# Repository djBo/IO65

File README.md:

# IO/65

IO/65, a modular hardware platform for the 6502 processor.

This project is very much inspired by [RC2014](https://rc2014.co.uk/) and Ben Eater's 6502 YouTube series.

### Table of Contents

   1. [History](#history)
   2. [Design](#design)
      * [Dimensions](#dimensions)
      * [Pinout](#pinout)
      * [Memory Map](#memory-map)
   3. [Boards](#boards)
      * [Backplane](#backplane)
      * [CPU](#cpu)
      * [Decoder](#address-decoder)
      * [Memory](#memory-module)
      * [VIA](#via)
      * [RIOT](#riot)
      * [Work in progress](#work-in-progress)
         - [ACIA](#acia)
         - [Audio](#audio)
         - [Banked Memory #1](#banked-memory-1)
         - [Banked Memory #2](#banked-memory-2)
         - [Buffered Memory](#buffered-memory)
         - [Dual-Port Memory](#dual-port-memory)
         - [Interrupt Controller](#interrupt-controller)
         - [PGA2040 Device](#pga2040-device)
         - [PGA2040 Emulator](#pga2040-emulator)
         - [Spy](#spy)
         - [Tape Interface](#tape-interface)
         - [UART](#uart-from-scratch)
         - [Video](#video-board)
         - [PC/104](#pc104)
      * [SBC](#sbc)
   4. [Footnotes](#footnotes)

### History

In the middle of the 2010's, I saved an Apple II-c from a dumpster. Sadly, without power supply, monitor or even software, there was no possibility of booting it directly.  
After a few searches on the interwebz, I came accross a breadboard circuit, allowing the 6502 in free running mode. So, I carefully removed the NCR 6502 CPU from it's socket, and placed it on a breadboard. I wired everything up, using a 555 as a rudimentary clock and a bunch of led bars on the address and data bus. I was intrigued by the flashy lights.

Then I stuble accross the [6502 primer](http://wilsonminesco.com/6502primer/)...  
It's a disguised Pandora's box! Inside you'll find an endless supply of more boxes, each containing countless more. It's a rabbit hole that never ends. Each box is a tiny bit of knowledge about a given subject you need to understand. The further you go, the more you need to figure out.

And so, starting with limited supplies, I opened the first box. The rest is history.

### Design

The original proof-of-concept board was based around the same use of angled pin headers as on RC2014. However, bent pins were a constant source of problems, not to mention the lack in quantity. Dual row headers were also considered, but this came with it's own connector problem of being very hard to remove and the increased risk of more bent pins. The set dimensions of the 40-pin wide header made the boards clunky. This meant that a simply back plane would quickly fall outside the cheapest 10x10mm manufacturing pricing.

The final design is centered around two specific standards:

 - the [ISO/IEC 7810](https://en.wikipedia.org/wiki/ISO/IEC_7810) standard, specifying the size of credit cards (amongst others) at 85.6mm by 53.98mm or 3+3⁄8" by 2+1⁄8". This was mostly inspired by several 6502 badges and the idea to carry one "in your wallet".
 - the PC/XT [ISA bus](https://en.wikipedia.org/wiki/Industry_Standard_Architecture) connector (a.k.a. [J1](https://nl.mouser.com/ProductDetail/571-6-5530843-5)). This was inspired by the fact that the edge connector width fits nicely in the middle of the card. A nice coincedence, is that the connector itself is pretty much as wide as the board, making them site nice and flush.

#### Dimensions

- Board: 85.6x54 mm
- Top corner radius: 3 mm
- Bottom corner radium: 1 mm
- Edge connector width: 81 mm
- Edge connector height: 300 mil
- Edge connector chamfer: 0,5 mm
- Edge connector bevelled: yes
- Edge connector location: bottom, centered on pin 16/47
- Thumb pocket radius: 13 mm
- Thumb pocket center: 10 mm from the top, 12 mm from the edge
- Work area center: 3,5 mm above card center
- Preferred OSHW logo location: 9,5 mm from the top, 10 mm from the right edge

An optional 2 mm wide cut-out slot on pin 17/48 is taken into account in the designs of the individual boards, forcing the board in a single direction. While the current backplane connects these pins allowing the boards to be rotated, it should be noted that __all boards need to face the same direction__ for the system to operate correctly.

#### Pinout

| Pin (Front) | Function | Pin (Back) | Function |
|----|----|----|----|
| 1 | GND | 32 | A0 |
| 2 | +5V | 33 | A1 |
| 3 | Φ2 | 34 | A2 |
| 4 | R/<span style="text-decoration: overline;">W</span> | 35 | A3 |
| 5 | <span style="text-decoration: overline;">RES</span> | 36 | A4 |
| 6 | RDY | 37 | A5 |
| 7 | <span style="text-decoration: overline;">IRQ</span> | 38 | A6 |
| 8 | <span style="text-decoration: overline;">NMI</span> | 39 | A7 |
| 9 | D0 | 40 | A8 |
| 10 | D1 | 41 | A9 |
| 11 | D2 | 42 | A10 |
| 12 | D3 | 43 | A11 |
| 13 | D4 | 44 | A12 |
| 14 | D5 | 45 | A13 |
| 15 | D6 | 46 | A14 |
| 16 | D7 | 47 | A15 |
| 17 | **NC** | 48 | **NC** |
| 18 | <span style="text-decoration: overline;">OE</span> | 49 | Unused [^1] |
| 19 | <span style="text-decoration: overline;">WE</span> | 50 | Unused |
| 20 | <span style="text-decoration: overline;">CS0</span> | 51 | VIA CB1 |
| 21 | <span style="text-decoration: overline;">CS1</span> | 52 | VIA CB2 |
| 22 | <span style="text-decoration: overline;">CS2</span> | 53 | VIA PB0 / RIOT PA0 |
| 23 | <span style="text-decoration: overline;">CS3</span> | 54 | VIA PB1 / RIOT PA1 |
| 24 | <span style="text-decoration: overline;">CS4</span> | 55 | VIA PB2 / RIOT PA2 |
| 25 | <span style="text-decoration: overline;">CS5</span> | 56 | VIA PB3 / RIOT PA3 |
| 26 | <span style="text-decoration: overline;">CS6</span> | 57 | VIA PB4 / RIOT PA4 |
| 27 | <span style="text-decoration: overline;">CS7</span> | 58 | VIA PB5 / RIOT PA5 |
| 28 | <span style="text-decoration: overline;">CS8</span> | 59 | VIA PB6 / RIOT PA6 |
| 29 | <span style="text-decoration: overline;">CS9</span> | 50 | VIA PB7 / RIOT PA7 |
| 30 | <span style="text-decoration: overline;">CS10</span> | 61 | +5V |
| 31 | <span style="text-decoration: overline;">CS11</span> | 62 | GND |

[^1]: For the two unused pins there are two possible options: serial Rx/Tx lines connected to the USB header on the back plane, or I^2^C.

#### Memory Map

Using the 6502 primer as guidance, the following design should be easy to implement and extend:

| Range | Description |
|---|---|
| 0x000-0x7FFF | 32K RAM |
| 0x8000-0x9FFF | 8K expansion (<span style="text-decoration: overline;">CS0</span>) |
| 0xA000-0xBFFF | 8K expansion (<span style="text-decoration: overline;">CS1</span>) |
| 0xC000-0xDFFF | 8K expansion (<span style="text-decoration: overline;">CS2</span>) |
| 0xE000-0xFFFF | 8K ROM (<span style="text-decoration: overline;">CS3</span>) |

### Boards

#### Backplane

The current iteration of the backplane crudely ties all lines of 8 slots (600 mil apart) together, exposing power pins through a two-pin header and optionally a MicroUSB connector, with data lines on another two-pin header. While it can certainly be used for initial design verification, it clearly needs a few upgrades like real power delivery and status leds.

#### CPU

The CPU board contains the 6502, 1MHz crystal, and a debounced button for the reset circuit. It can be configured to be used with either older or newer CPU's, reconfiguring the pins for BE and <span style="text-decoration: overline;">VP</span>. It exposes the oscillator output, Φ0 input, and the SYNC/<span style="text-decoration: overline;">SO</span>/<span style="text-decoration: overline;">VP</span>/BE signals to a 6-pin header. They can be used to provide external clocks or single-cycle/single-instruction stepping capabilities.

Under normal use, a jumper should connect the oscillator output and Φ0 input together.

#### Address Decoder

The address decoder is responsible for providing a usuable memory map, and providing signals for <span style="text-decoration: overline;">OE</span>, <span style="text-decoration: overline;">WE</span> and <span style="text-decoration: overline;">CS0</span> to <span style="text-decoration: overline;">CS11</span>.

<span style="text-decoration: overline;">OE</span> and <span style="text-decoration: overline;">WE</span> are generated by using R/<span style="text-decoration: overline;">W</span> and Φ2. <span style="text-decoration: overline;">CS0</span> to <span style="text-decoration: overline;">CS3</span> are directly mapped to the first stage decoder, giving each section 8k (see the [memory map](#memory-map) above).

The second stage decoder breaks the 0xC000-0xDFFF range down into 8 sections of 1k. These are exposed on a separate 8-pin header.  
The third stage decoder breaks down two configurable regions into 4 sections of 256 bytes. These two ranges are tied into <span style="text-decoration: overline;">CS4</span> to <span style="text-decoration: overline;">CS11</span>:

| Region | 3 | ∆ |
|---|---|---|
| 1 | 0xC000-0xC3FF | 0xD800-0xDBFF |
| 2 | 0xD000-0xD3FF | 0xDC00-oxDFFF |

#### Memory Module

The memory module is a configurable 8k or 32k single chip (DIP28) design, allowing it to be placed in either the RAM range or any of the 8k ranges. An optional 2-pin dip-switch or header can be soldered to accommodate 32k EEPROMS with manual banking.

#### VIA

The Versatile Interface Adapter (a.k.a. 6522) provides 2 16-bit programmable timers and two 8-bit ports with two control lines each. It exposes PORTA and control lines on a 10-pin header and PORTB and control lines on the rear of the edge connector. PORTB was chosen as it is connected to the onboard shift register, allowing extended capabilities in combination with other board circuits.

#### RIOT

The RAM, IO and Timer (a.k.a. 6532) provides 128 bytes of general purpose RAM, programmable interval timer and two 8-bit IO ports. It exposes PORTB on an 8-pin header and PORTA on the rear of the edge connector. While PORTB can drive more current (and thus more suited for driving external circuitry), PORTA has an additional edge-detect capability on PA7.

#### Work in progress

The following boards are very much *in development*:

##### ACIA

The Asynchronous Communications Interface Adapter (a.k.a. 6551) provides serial communication. It is intended to be used with a Serial-to-USB device.

##### Audio

The audio board consists of two [SN76489](https://en.wikipedia.org/wiki/Texas_Instruments_SN76489)'s for stereo 3 channel PSG and 1 channel noise.

##### Banked Memory #1

This board banks 2 MB of RAM in 256 8k blocks. This is specifically meant for <span style="text-decoration: overline;">CS1</span> or <span style="text-decoration: overline;">CS2</span>.

##### Banked Memory #2

This board banks 8 MB in 256 32k blocks. This is specifically meant to occupy the RAM region.

##### Buffered Memory

This board contains 2 8k RAM chips. All control lines are attached in a cross fashion to both the edge connector and a 22-pin header for external circuitry. While one chip is connected to the edge, the other is connected to the header. Ths can be swicthed using a single 1-bit register. This is specifically meant for the <span style="text-decoration: overline;">CS2</span> region in conjuncion with the below mentioned video output card.

##### Dual-Port Memory

This board contains a single dual-port 8k SRAM ic. One side is connected to the edge connector (read/write), while the other is exposed on a 22-pin header for external circuitry. This is specifically meant for the <span style="text-decoration: overline;">CS2</span> region in conjuncion with the below mentioned video output card.

##### Interrupt Controller

This board is from Paul Fellingham's [design](http://6502.org/mini-projects/priority-interrupt-encoder/priority-interrupt-encoder.html), and provides 8 prioritized interrupt inputs on a header.  
Future designs of interrupt capable boards will introduce additional configuration options and IRQ line exposure using a single pin header (similar to how CS is done).

##### PGA2040 Device

This board contains a [PGA2040](https://shop.pimoroni.com/products/pga2040) with 10 pins connected through voltage converters to CS, R/W and data bus signals. This board is meant to be utilized as an addressable device.

##### PGA2040 Emulator

This board contains a [PGA2040](https://shop.pimoroni.com/products/pga2040) utilizing all 30 available pins to the edge connector. This board is meant as a CPU replacement, and act as a full-scale 6502 emulator.

##### Spy

The Spy board contains all the required circuitry to implement adjustable clocks, single-cycle/single-instruction stepping and a hexadecimal display of the address/data bus values using TIL311's. This board is explicitly meant to be used in conjunction with a new 65C02 CPU with the BE and <span style="text-decoration: overline;">VP</span> pins. **Do not use with NMOS 6502's!**

##### Tape Interface

This board implements a Kansas City Standard tape decoder interface. See [this project](https://www.gregorystrike.com/2023/01/07/kansas-city-standard-decoder/) and this [Hackaday topic](https://hackaday.com/2022/10/11/a-cassette-interface-for-a-6502-breadboard-computer-kansas-city-style/) for more information.

##### UART from scratch

The board is based on James Sharman's amazing youtube series [UART from scratch](https://www.youtube.com/watch?v=aE5VTp_eMN4&list=PLFhc0MFC8MiCs8W5H0qZlC6QNbpAAe_O-&pp=iAQB).

##### Video Board

This board contains a [MC6847](https://en.wikipedia.org/wiki/Motorola_6847) VDG with a MC1372 modulator, and can be used to output a video signal. It is meant to be used together with the above mentioned Buffered Memory or Dual-Port Memory boards. All designs come straight from [@pmig96](https://twitter.com/pmig96)'s series of articles on the subject:

* [MC6874 Test Circuit #1](https://pmig96.wordpress.com/2020/07/15/mc6847-test-circuit/)
* [MC6874 Test Circuit #2](https://pmig96.wordpress.com/2020/07/16/mc6847-test-circuit-part-2/)
* [MC6874 Test Circuit #3](https://pmig96.wordpress.com/2020/07/24/mc6847-test-circuit-part-3/)
* [MC6874 Test Circuit #4](https://pmig96.wordpress.com/2020/07/27/mc6847-test-circuit-part-4/)
* [MC6874 Test Circuit #5](https://pmig96.wordpress.com/2022/04/01/mc6847-test-circuit-part-5/)
* [MC6874 Test Circuit #6](https://pmig96.wordpress.com/2022/04/05/mc6847-test-circuit-part-6/)
* [MC6874 Test Circuit #7](https://pmig96.wordpress.com/2022/04/07/mc6847-test-circuit-part-7/)
* [MC6874 Test Circuit #8](https://pmig96.wordpress.com/2022/08/22/mc6847-test-circuit-part-8/)
* [MC6874 Dual-Port RAM](https://pmig96.wordpress.com/2020/08/20/a-dual-ported-ram-for-the-mc6847/)

Sadly, there is not much info out there regarding this chip. Worst of all, mine *seems* to be misbehaving, as I am not able to reproduce the nice black-and-white image from part 1 (it's all wavy side to side).

##### PC/104

This board is mostly a proof-of-concept, trying to adapt the 6502 platform to the the PC/104 form-factor. While not all signals can be re-created, most of them can be provided.

#### SBC

This board is designed to combined several cards into a single-board-computer and uses only SMD components. It's meant to be a badge, capable of running from a single 18550 battery. This is the culmination of months of designing all the other boards, and making a version that has everything already integrated. By utilizing the tiniest of chips, the board is capable of housing a fairly involved set of capabilities.

**Features:**

* QFN-44 packaged WDC 65C02 CPU
* QFN-44 packaged WDC 65C22 VIA
* 1MHz Clock
* 32Kb SRAM
* 8Kb FRAM
* configurable decoder logic
* single-cycle/single-instruction stepping
* blinkin' leds everywhere
* powered by USB or 18650 battery with seemless switching
* battery charging with USB or solar
* firmware upgrading through USB

**Design considerations:**  
Almost none of these parts can be hand-soldered, so stencils for both sides are required. Note the use of 0402 sized resistors, capacitors and leds. The board complexity also requires at least 4 layers, with real layer-to-layer via's.

For power delivery, a simple integrated ic would be nice. However, a single ic incorporating USB/Solar charging, buck-boost conversion, seemless switching and interrupt capability might prove hard to find. Any suggestions are welcome.

Firmware upgrading is an entire new can-o-worms. Some FTDI chips seem to be capable of doing the job, but custom host-based software will probably be required. It will need to connect to the BE signal (and possibly RST/RDY too) in order to take full bus-control. Another contention issue is the size and pricing of FRAM: 32K is about $ 14 each, while 8k is about half.

While the WDC 65C51N is available is a nice QFP-32 package, it suffers from the transmit data register bug and was omitted in the initial design. Also, Mouser only has the DIP & PLCC versions.

LED control could possibly be accomplished with the VIA PORTB's shift-register feature. This would mean swapping the ports around from the original board and needs some serious reconsideration before going down that route.  
The core mechanic is to provide generic control using PORTA, optionally extending it to hardware based RGB control.

Memory could possibly be increased by adding one or two cheap 8k SRAM ic's. 

**BoM**:

| Nr | Description | Part Nr. | Power | Price |
|---|---|---|---|---|
| 1 | WDC 65C02 | [W65C02S6TQG-14](https://nl.mouser.com/ProductDetail/955-W65C02S6TQG-14) | 150uA@1MHz | € 9,88 |
| 1 | WDC 65C02 | [W65C22S6TQG-14](https://nl.mouser.com/ProductDetail/955-W65C22S6TQG-14) || € 10,21 |
| 1 | FRAM 8Kb | [FM16W08-SG](https://nl.mouser.com/ProductDetail/877-FM16W08-SG) || € 6,50 |
| 1 | SRAM 32Kb | [AS7C256A-10TCN](https://nl.mouser.com/ProductDetail/913-AS7C256A-10TCN) || € 2,30 |
| 1 | 1MHz Oscillator | [LFSPXO058610Reel](https://nl.mouser.com/ProductDetail/449-LFSPXO058610REEL) or [CB3-3C-1M000000](https://nl.mouser.com/ProductDetail/774-CB3-3C-1M000000) || € 1,36 / 1,59 |
| 1 | Battery Management IC | [MAX8903](https://nl.mouser.com/ProductDetail/700-MAX8903DETI+) || € 7,06 |
| 8 | Green LED 0402 | Data Bus || ... |
| 16 | Red LED 0402 | Address Bus || ... |
| 8 | White, Blue or RGB LED 0402 | VIA PORT A || ... |
| 2 | Inverter | [SN74AHCT1G04DBVR](595-SN74AHCT1G04DBVR) SOT-23-5 || € 0,348 |
| 2 | Dual 2-to-4 line decoder | [SN74HCT139DE4](https://nl.mouser.com/ProductDetail/595-SN74HCT139DE4) || € 1,21 |
| 1 | 3-to-8 line decoder | [MC74HCT138ADG](https://nl.mouser.com/ProductDetail/863-MC74HCT138ADG) || €  |
| 1 | USB-to-Parallel | [FT245RL](https://nl.mouser.com/ProductDetail/895-FT245RL) (SSOP-28) or [FT245RQ](https://nl.mouser.com/ProductDetail/895-FT245RQ-TRAY) (QFN-32) || € 4,51 |
| 1 | SRAM 2Mb | [CY62167GN-45ZXI](https://nl.mouser.com/ProductDetail/727-CY62167GN-45ZXI) || € 13,24 |

To be considered:
| Nr | Description | Part Nr. | Price |
|---|---|---|---|
| 1 | 18650 Battery Clip | [12BHC186P1-GR](https://nl.mouser.com/ProductDetail/12BHC186P1-GR) | € 3,30 |
| 1 | Solar Battery Charger IC | [SPV1040T](https://nl.mouser.com/ProductDetail/511-SPV1040T) | € 4,19 |
| 1 | 3.3V Voltage Reference | [MCP1501T-33E/CHY](https://nl.mouser.com/ProductDetail/579-MCP1501T-33E/CHY) | € 0.94 |
| 1 | 3.3V Voltage Reference | [MAX6070BAUT33+T](https://nl.mouser.com/ProductDetail/700-MAX6070BAUT33T) | € 2.61 |
| 1 | 3.3V Voltage Reference | [ADR3533WARMZ-R7](https://nl.mouser.com/ProductDetail/584-ADR3533WARMZ-R7) | € 3.72 |
| 1 | 3.3V Voltage Reference | [ADR4533ARZ](https://nl.mouser.com/ProductDetail/584-ADR4533ARZ) | € 7.36 |
| 8 | Tri-Color LED | [APGF1012GBRC-07](https://nl.mouser.com/ProductDetail/604-APGF1012GBRC-07) | € 0,987 |
| 8 | RGB LED | [LRTBR48G-P9Q7-1+R7S5-26+NP-68](https://nl.mouser.com/ProductDetail/720-LRTBR48GP9A3521) | € 0,385 |
| 1 | USB Type-C Connector | | € 0,63 + |
| 1 | Parallel I^2^C Controller | [PCF8584T/2,512](https://nl.mouser.com/ProductDetail/771-PCF8584T2512) | € 6,58 |

### Footnotes

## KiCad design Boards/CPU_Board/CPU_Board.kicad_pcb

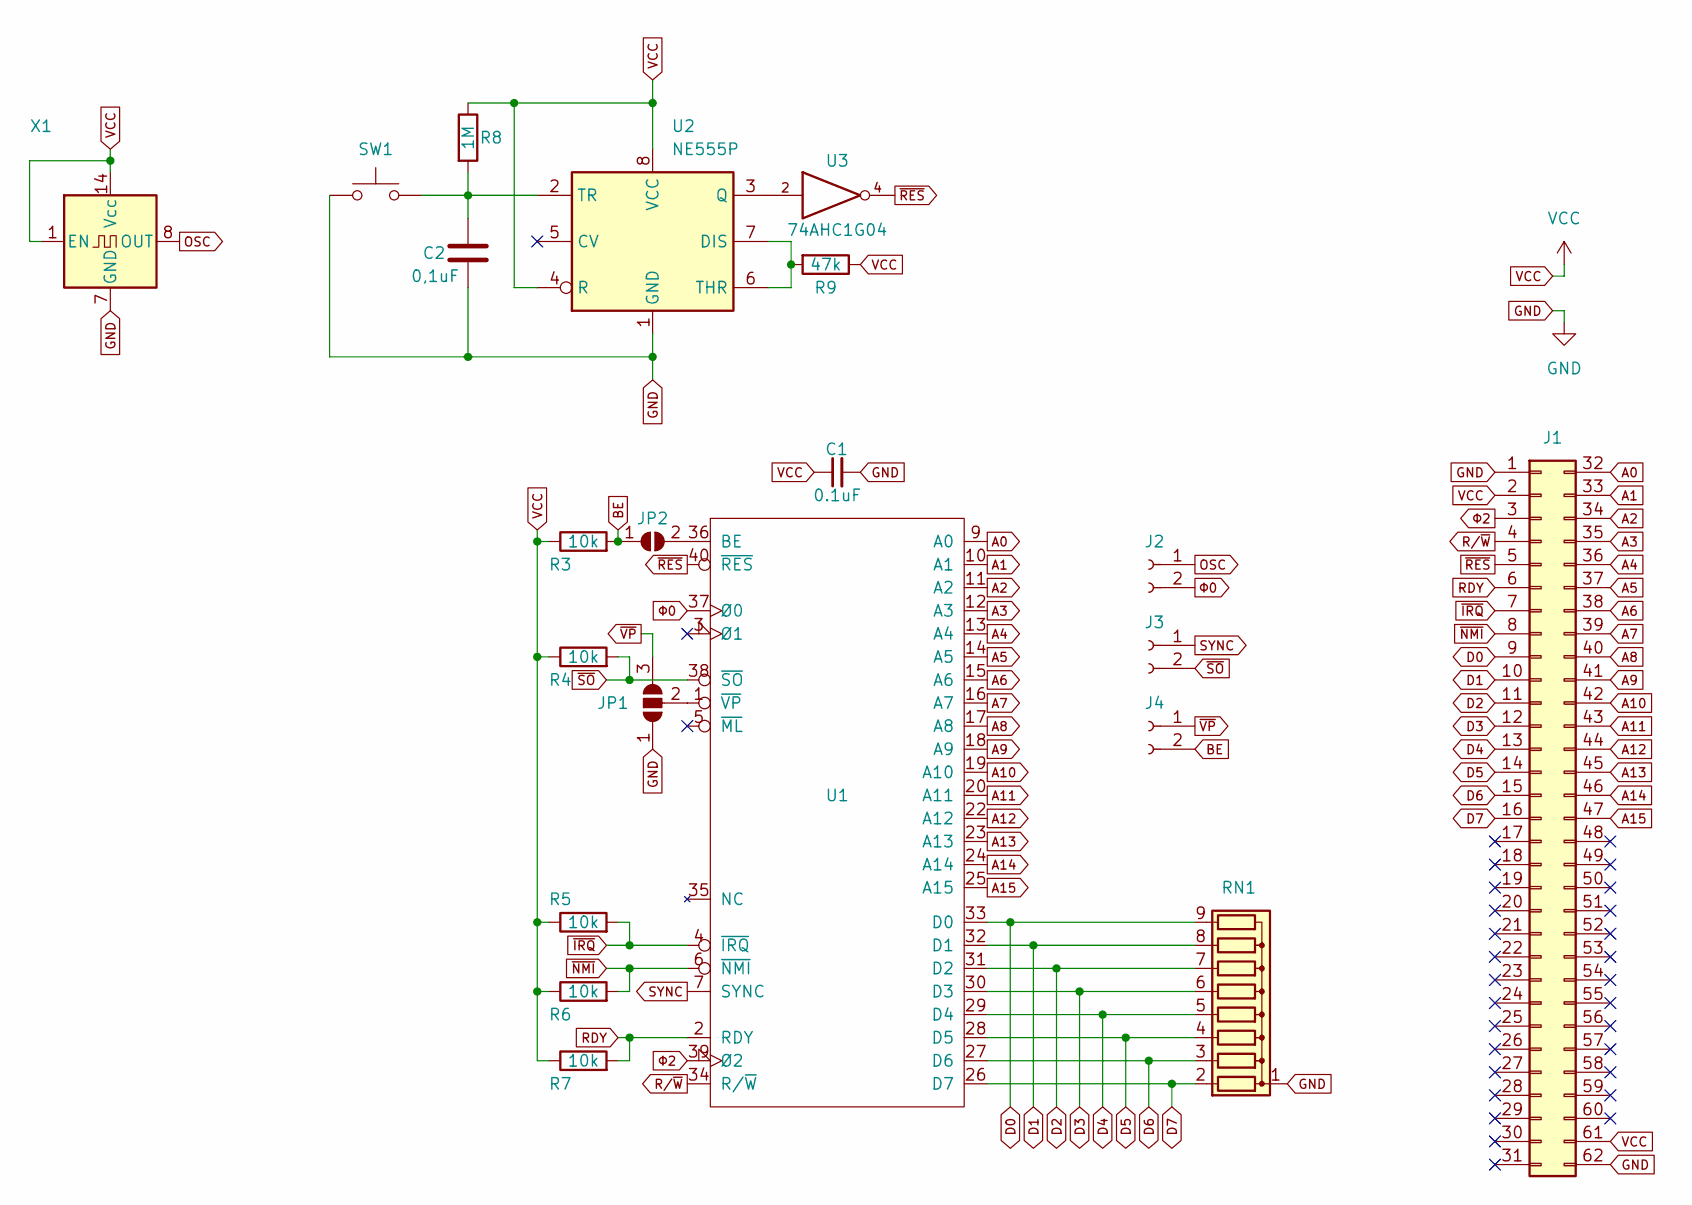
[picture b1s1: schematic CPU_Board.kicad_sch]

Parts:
C1: 0.1uF; C_Disc_D4.7mm_W2.5mm_P5.00mm
C2: 0,1uF; C_Disc_D4.7mm_W2.5mm_P5.00mm
J1: Edge Connector; BUS_PC_M
J2, J3, J4: Conn_01x02_Female; PinSocket_1x02_P2.54mm_Horizontal
JP1: SolderJumper_3_Open; SolderJumper-3_P1.3mm_Open_Pad1.0x1.5mm
JP2: SolderJumper_2_Open; SolderJumper-2_P1.3mm_Open_Pad1.0x1.5mm
R3, R4, R5, R6, R7: 10k; R_Axial_DIN0207_L6.3mm_D2.5mm_P7.62mm_Horizontal
R8: 1M; R_Axial_DIN0207_L6.3mm_D2.5mm_P7.62mm_Horizontal
R9: 47k; R_Axial_DIN0207_L6.3mm_D2.5mm_P7.62mm_Horizontal
RN1: 10k; R_Array_SIP9
SW1: SW_Push; SW_Tactile_SPST_Angled_PTS645Vx39-2LFS
U1: WDC65C02_DIP; DIP-40_W15.24mm_Socket
U2: NE555P; DIP-8_W7.62mm_Socket
U3: 74AHC1G04; SOT-23-5
X1: CXO_DIP14; Oscillator_DIP-14

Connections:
A0: J1.32, U1.9 (A0)
A1: J1.33, U1.10 (A1)
A2: J1.34, U1.11 (A2)
A3: J1.35, U1.12 (A3)
A4: J1.36, U1.13 (A4)
A5: J1.37, U1.14 (A5)
A6: J1.38, U1.15 (A6)
A7: J1.39, U1.16 (A7)
A8: J1.40, U1.17 (A8)
A9: J1.41, U1.18 (A9)
A10: J1.42, U1.19 (A10)
A11: J1.43, U1.20 (A11)
A12: J1.44, U1.22 (A12)
A13: J1.45, U1.23 (A13)
A14: J1.46, U1.24 (A14)
A15: J1.47, U1.25 (A15)
BE: J4.2, JP2.1 (A), R3.2
D0: J1.9, RN1.9 (R8), U1.33 (D0)
D1: J1.10, RN1.8 (R7), U1.32 (D1)
D2: J1.11, RN1.7 (R6), U1.31 (D2)
D3: J1.12, RN1.6 (R5), U1.30 (D3)
D4: J1.13, RN1.5 (R4), U1.29 (D4)
D5: J1.14, RN1.4 (R3), U1.28 (D5)
D6: J1.15, RN1.3 (R2), U1.27 (D6)
D7: J1.16, RN1.2 (R1), U1.26 (D7)
GND: C1.2, C2.2, J1.1, J1.62, JP1.1 (A), RN1.1 (common), SW1.1, U1.21 (GND), U2.1 (GND), U3.3 (GND), X1.7 (GND)
unnamed: C2.1, R8.2, SW1.2, U2.2 (TR)
unnamed: JP1.2 (C), U1.1 (~VP)
unnamed: JP2.2 (B), U1.36 (BE)
unnamed: R9.2, U2.6 (THR), U2.7 (DIS)
unnamed: U2.3 (Q), U3.2
OSC: J2.1, X1.8 (OUT)
RDY: J1.6, R7.2, U1.2 (RDY)
SYNC: J3.1, U1.7 (SYNC)
VCC: C1.1, J1.2, J1.61, R3.1, R4.1, R5.1, R6.1, R7.1, R8.1, R9.1, U1.8 (VCC), U2.4 (R), U2.8 (VCC), U3.5 (VCC), X1.1 (EN), X1.14 (Vcc)
~IRQ: J1.7, R5.2, U1.4 (~IRQ)
~NMI: J1.8, R6.2, U1.6 (~NMI)
~RES: J1.5, U1.40 (~RES), U3.4
~SO: J3.2, R4.2, U1.38 (~SO)
~VP: J4.1, JP1.3 (B)
Φ0: J2.2, U1.37 (Ø0)
Φ2: J1.3, U1.39 (Ø2)

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
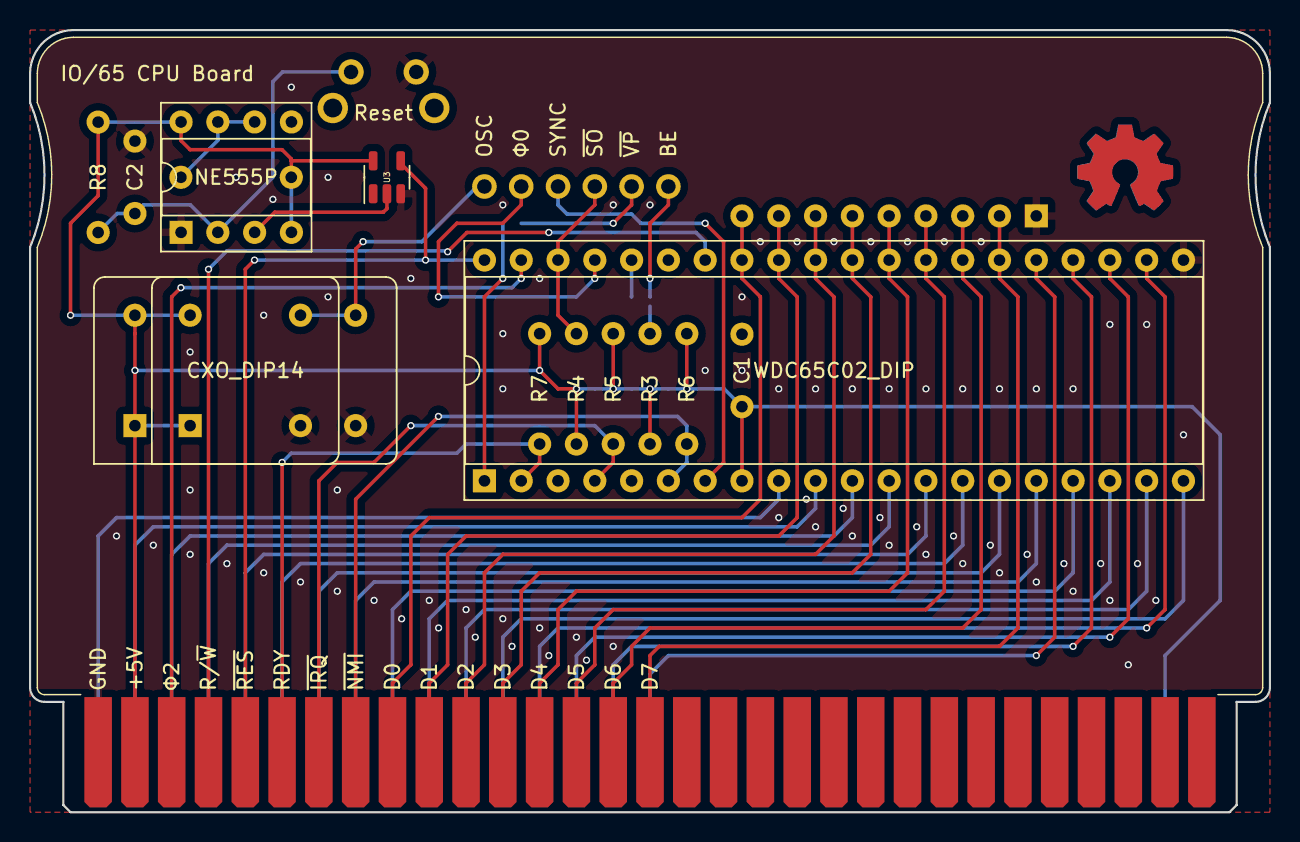
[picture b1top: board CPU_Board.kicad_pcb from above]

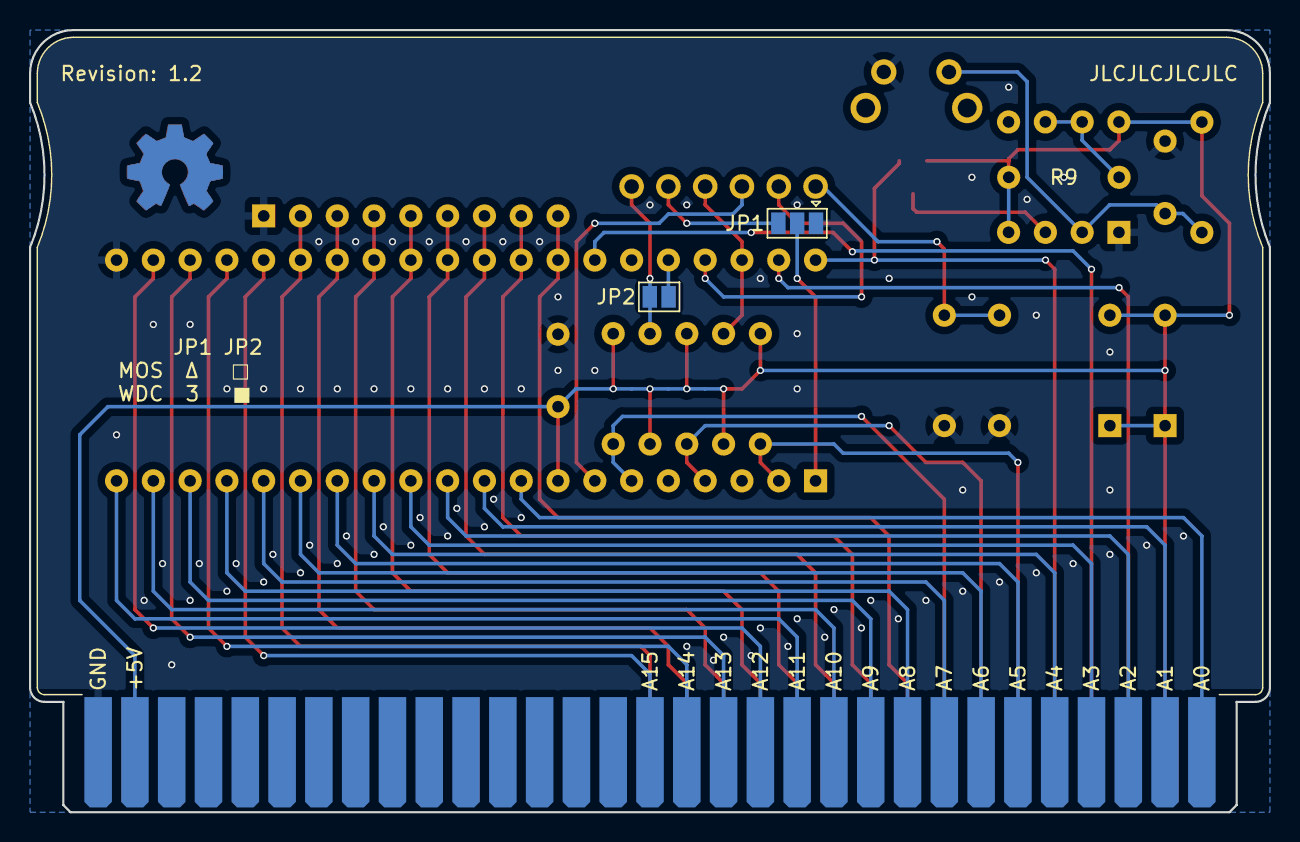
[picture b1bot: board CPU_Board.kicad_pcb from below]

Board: 2 copper layers, 85.6 x 54.0 mm, 25 parts (9 on the bottom side), 43 nets.

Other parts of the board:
LogoBack: OSHW-Symbol_6.7x6mm_Copper
LogoBackMask: OSHW-Symbol_6.7x6mm_Copper
LogoFront: OSHW-Symbol_6.7x6mm_Copper
LogoFrontMask: OSHW-Symbol_6.7x6mm_Copper

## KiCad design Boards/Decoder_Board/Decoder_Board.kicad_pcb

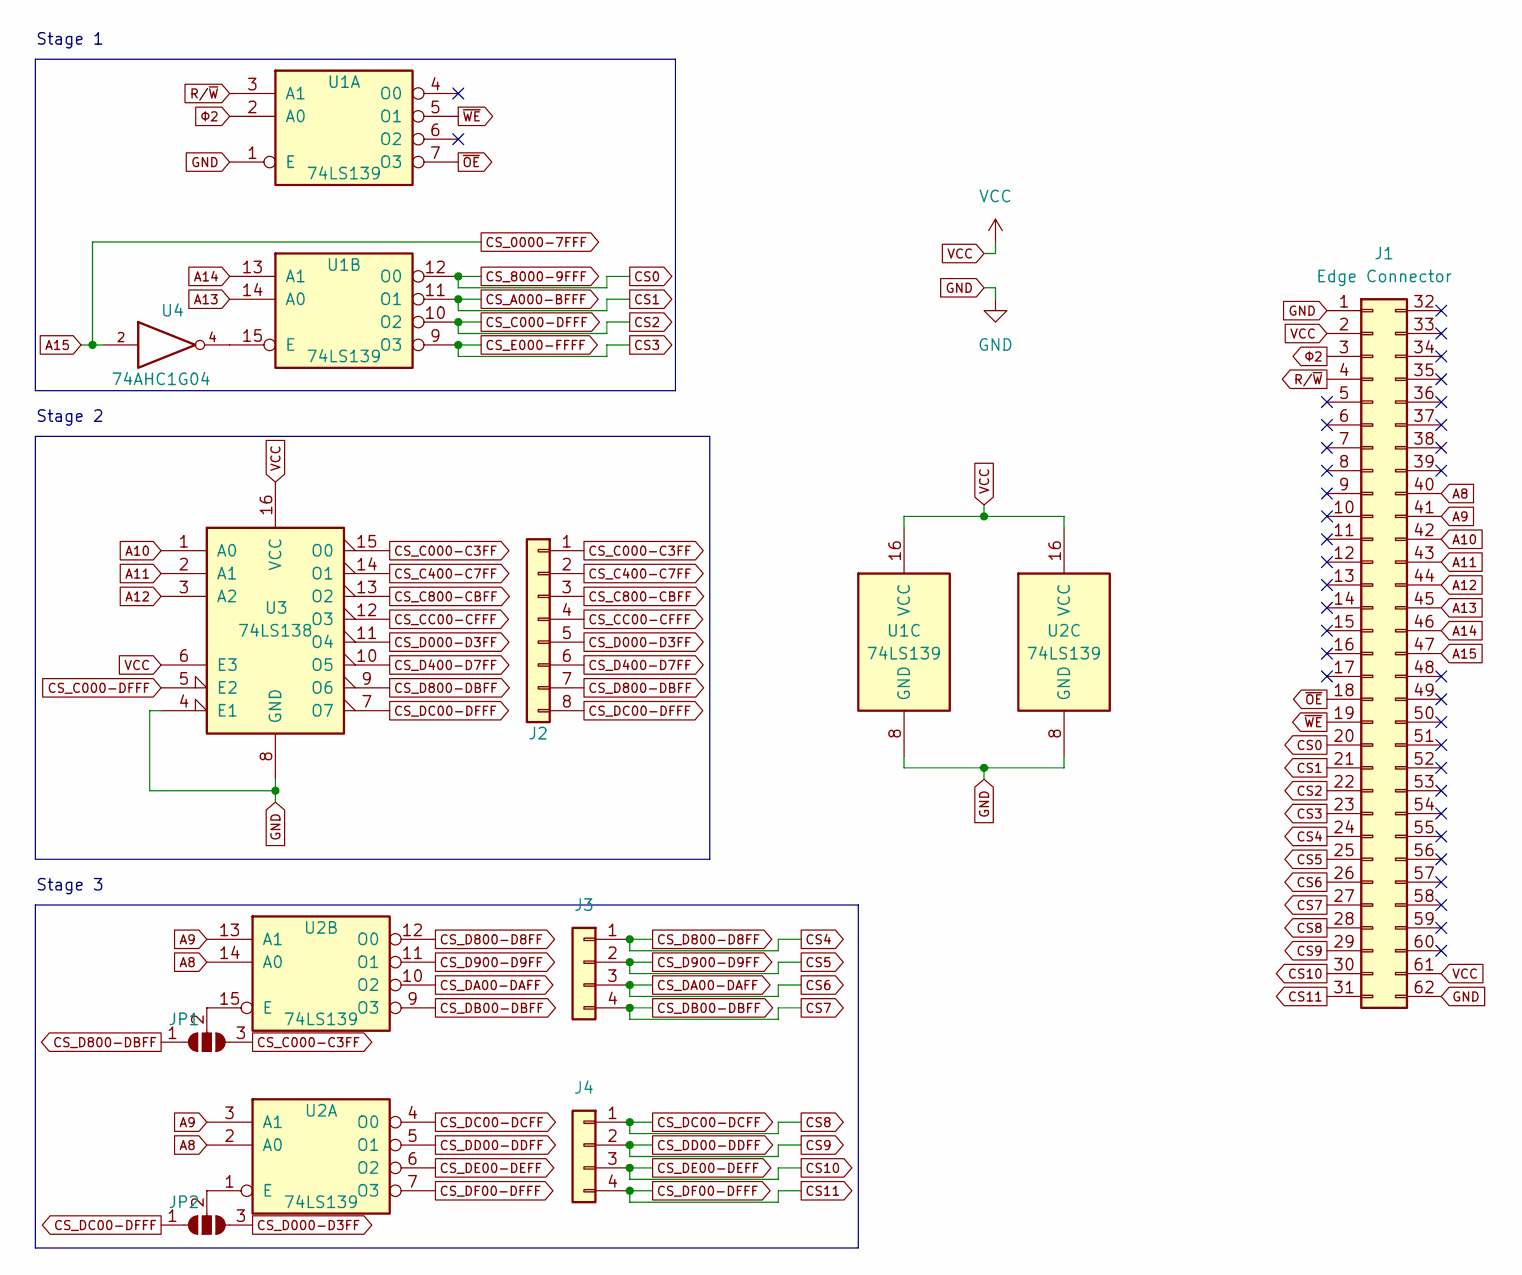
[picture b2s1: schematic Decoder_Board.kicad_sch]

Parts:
J1: Edge Connector; BUS_PC_M
J2: Conn_01x08; PinSocket_1x08_P2.54mm_Horizontal
J3, J4: Conn_01x04; PinSocket_1x04_P2.54mm_Horizontal
JP1, JP2: SolderJumper_3_Open; SolderJumper-3_P1.3mm_Open_Pad1.0x1.5mm
U1, U2: 74LS139; DIP-16_W7.62mm_Socket
U3: 74LS138; DIP-16_W7.62mm_Socket
U4: 74AHC1G04; SOT-23-5

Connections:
A8: J1.40, U2.2 (A0), U2.14 (A0)
A9: J1.41, U2.3 (A1), U2.13 (A1)
A10: J1.42, U3.1 (A0)
A11: J1.43, U3.2 (A1)
A12: J1.44, U3.3 (A2)
A13: J1.45, U1.14 (A0)
A14: J1.46, U1.13 (A1)
A15: J1.47, U4.2
CS0: J1.20, U1.12 (O0)
CS1: J1.21, U1.11 (O1)
CS2: J1.22, U1.10 (O2), U3.5 (E2)
CS3: J1.23, U1.9 (O3)
CS4: J1.24, J3.1, U2.12 (O0)
CS5: J1.25, J3.2, U2.11 (O1)
CS6: J1.26, J3.3, U2.10 (O2)
CS7: J1.27, J3.4, U2.9 (O3)
CS8: J1.28, J4.1, U2.4 (O0)
CS9: J1.29, J4.2, U2.5 (O1)
CS10: J1.30, J4.3, U2.6 (O2)
CS11: J1.31, J4.4, U2.7 (O3)
CS_C000-C3FF: J2.1, JP1.3 (B), U3.15 (O0)
CS_C400-C7FF: J2.2, U3.14 (O1)
CS_C800-CBFF: J2.3, U3.13 (O2)
CS_CC00-CFFF: J2.4, U3.12 (O3)
CS_D000-D3FF: J2.5, JP2.3 (B), U3.11 (O4)
CS_D400-D7FF: J2.6, U3.10 (O5)
CS_D800-DBFF: J2.7, JP1.1 (A), U3.9 (O6)
CS_DC00-DFFF: J2.8, JP2.1 (A), U3.7 (O7)
GND: J1.1, J1.62, U1.1 (E), U1.8 (GND), U2.8 (GND), U3.4 (E1), U3.8 (GND), U4.3 (GND)
unnamed: JP1.2 (C), U2.15 (E)
unnamed: JP2.2 (C), U2.1 (E)
unnamed: U1.15 (E), U4.4
R/~W: J1.4, U1.3 (A1)
VCC: J1.2, J1.61, U1.16 (VCC), U2.16 (VCC), U3.6 (E3), U3.16 (VCC), U4.5 (VCC)
~OE: J1.18, U1.7 (O3)
~WE: J1.19, U1.5 (O1)
Φ2: J1.3, U1.2 (A0)

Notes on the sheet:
Stage 2
Stage 1
Stage 3

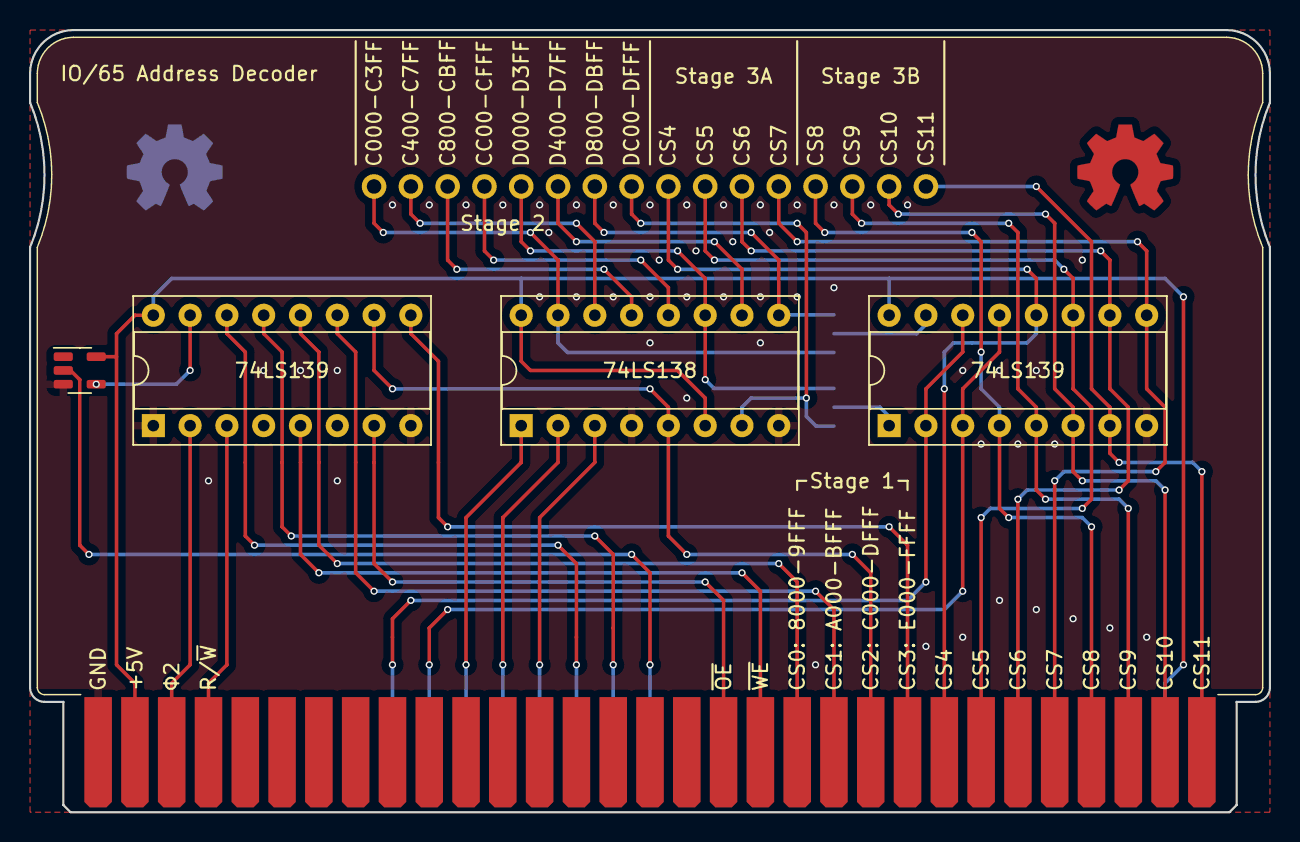
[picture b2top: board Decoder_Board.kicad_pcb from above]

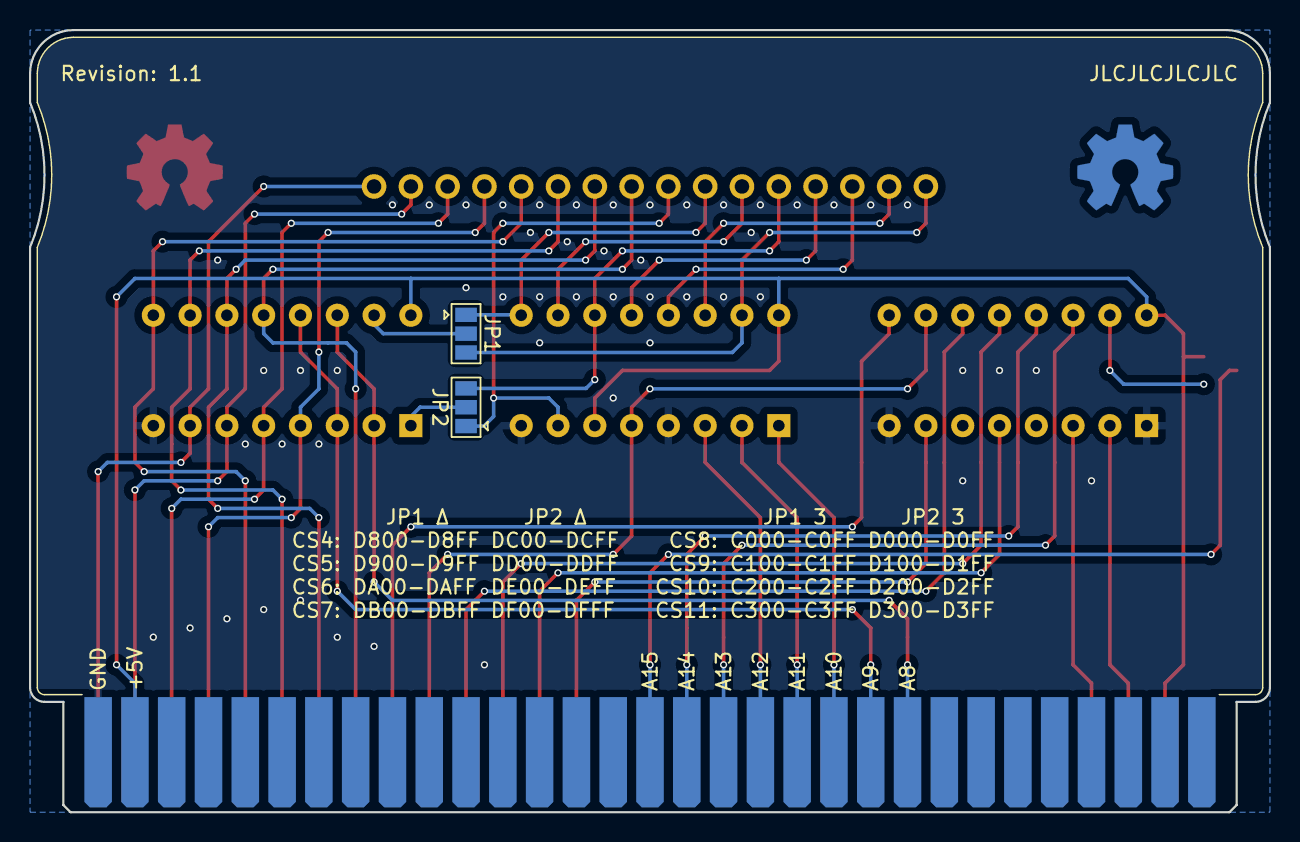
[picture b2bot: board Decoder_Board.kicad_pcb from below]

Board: 2 copper layers, 85.6 x 54.0 mm, 14 parts (7 on the bottom side), 37 nets.

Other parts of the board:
LogoBack: OSHW-Symbol_6.7x6mm_Copper
LogoBackMask: OSHW-Symbol_6.7x6mm_Copper
LogoFront: OSHW-Symbol_6.7x6mm_Copper
LogoFrontMask: OSHW-Symbol_6.7x6mm_Copper

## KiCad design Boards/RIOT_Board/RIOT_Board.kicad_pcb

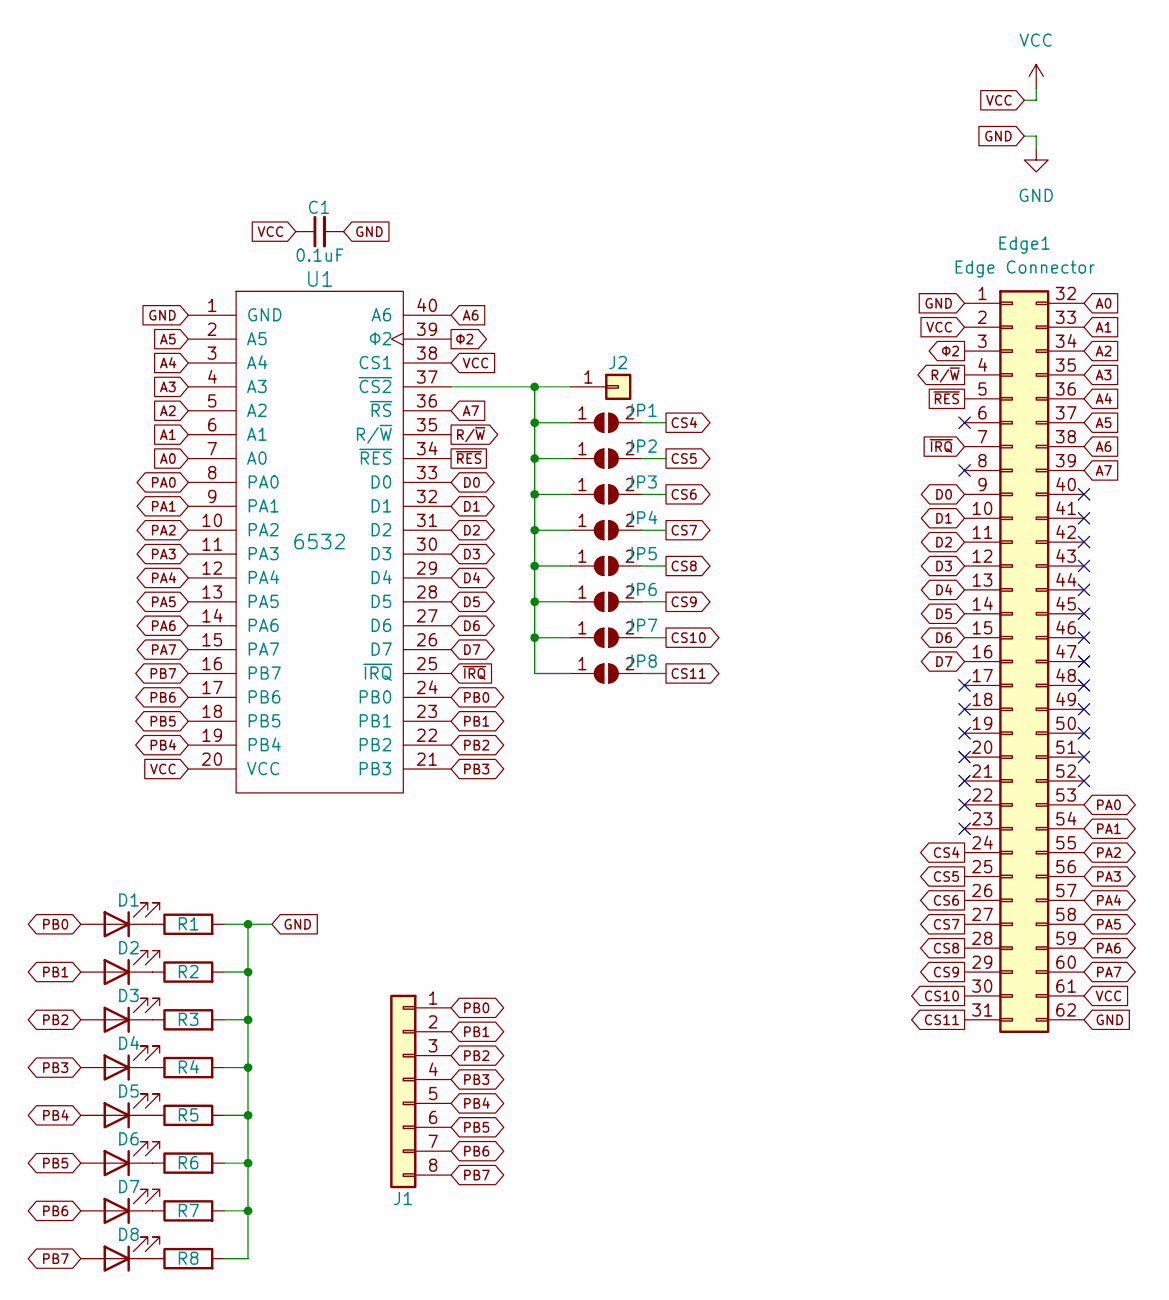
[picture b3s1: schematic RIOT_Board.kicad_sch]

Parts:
C1: 0.1uF; C_Disc_D4.7mm_W2.5mm_P5.00mm
D1, D2, D3, D4, D5, D6, D7, D8: LED; LED_0603_1608Metric_Pad1.05x0.95mm_HandSolder
Edge1: Edge Connector; BUS_PC_M
J1: Conn_01x08; PinSocket_1x08_P2.54mm_Horizontal
J2: Conn_01x01; PinSocket_1x01_P2.54mm_Horizontal
JP1, JP2, JP3, JP4, JP5, JP6, JP7, JP8: SolderJumper_2_Open; SolderJumper-2_P1.3mm_Open_Pad1.0x1.5mm
R1, R2, R3, R4, R5, R6, R7, R8: R; R_0603_1608Metric_Pad0.98x0.95mm_HandSolder
U1: 6532; DIP-40_W15.24mm_Socket

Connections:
A0: Edge1.32, U1.7 (A0)
A1: Edge1.33, U1.6 (A1)
A2: Edge1.34, U1.5 (A2)
A3: Edge1.35, U1.4 (A3)
A4: Edge1.36, U1.3 (A4)
A5: Edge1.37, U1.2 (A5)
A6: Edge1.38, U1.40 (A6)
A7: Edge1.39, U1.36 (~RS)
CS4: Edge1.24, JP1.2 (B)
CS5: Edge1.25, JP2.2 (B)
CS6: Edge1.26, JP3.2 (B)
CS7: Edge1.27, JP4.2 (B)
CS8: Edge1.28, JP5.2 (B)
CS9: Edge1.29, JP6.2 (B)
CS10: Edge1.30, JP7.2 (B)
CS11: Edge1.31, JP8.2 (B)
D0: Edge1.9, U1.33 (D0)
D1: Edge1.10, U1.32 (D1)
D2: Edge1.11, U1.31 (D2)
D3: Edge1.12, U1.30 (D3)
D4: Edge1.13, U1.29 (D4)
D5: Edge1.14, U1.28 (D5)
D6: Edge1.15, U1.27 (D6)
D7: Edge1.16, U1.26 (D7)
GND: C1.2, Edge1.1, Edge1.62, R1.2, R2.2, R3.2, R4.2, R5.2, R6.2, R7.2, R8.2, U1.1 (GND)
unnamed: D1.1 (K), R1.1
unnamed: D2.1 (K), R2.1
unnamed: D3.1 (K), R3.1
unnamed: D4.1 (K), R4.1
unnamed: D5.1 (K), R5.1
unnamed: D6.1 (K), R6.1
unnamed: D7.1 (K), R7.1
unnamed: D8.1 (K), R8.1
unnamed: J2.1, JP1.1 (A), JP2.1 (A), JP3.1 (A), JP4.1 (A), JP5.1 (A), JP6.1 (A), JP7.1 (A), JP8.1 (A), U1.37 (~CS2)
PA0: Edge1.53, U1.8 (PA0)
PA1: Edge1.54, U1.9 (PA1)
PA2: Edge1.55, U1.10 (PA2)
PA3: Edge1.56, U1.11 (PA3)
PA4: Edge1.57, U1.12 (PA4)
PA5: Edge1.58, U1.13 (PA5)
PA6: Edge1.59, U1.14 (PA6)
PA7: Edge1.60, U1.15 (PA7)
PB0: D1.2 (A), J1.1, U1.24 (PB0)
PB1: D2.2 (A), J1.2, U1.23 (PB1)
PB2: D3.2 (A), J1.3, U1.22 (PB2)
PB3: D4.2 (A), J1.4, U1.21 (PB3)
PB4: D5.2 (A), J1.5, U1.19 (PB4)
PB5: D6.2 (A), J1.6, U1.18 (PB5)
PB6: D7.2 (A), J1.7, U1.17 (PB6)
PB7: D8.2 (A), J1.8, U1.16 (PB7)
R/~W: Edge1.4, U1.35 (R/~W)
VCC: C1.1, Edge1.2, Edge1.61, U1.20 (VCC), U1.38 (CS1)
~IRQ: Edge1.7, U1.25 (~IRQ)
~RES: Edge1.5, U1.34 (~RES)
Φ2: Edge1.3, U1.39 (Φ2)

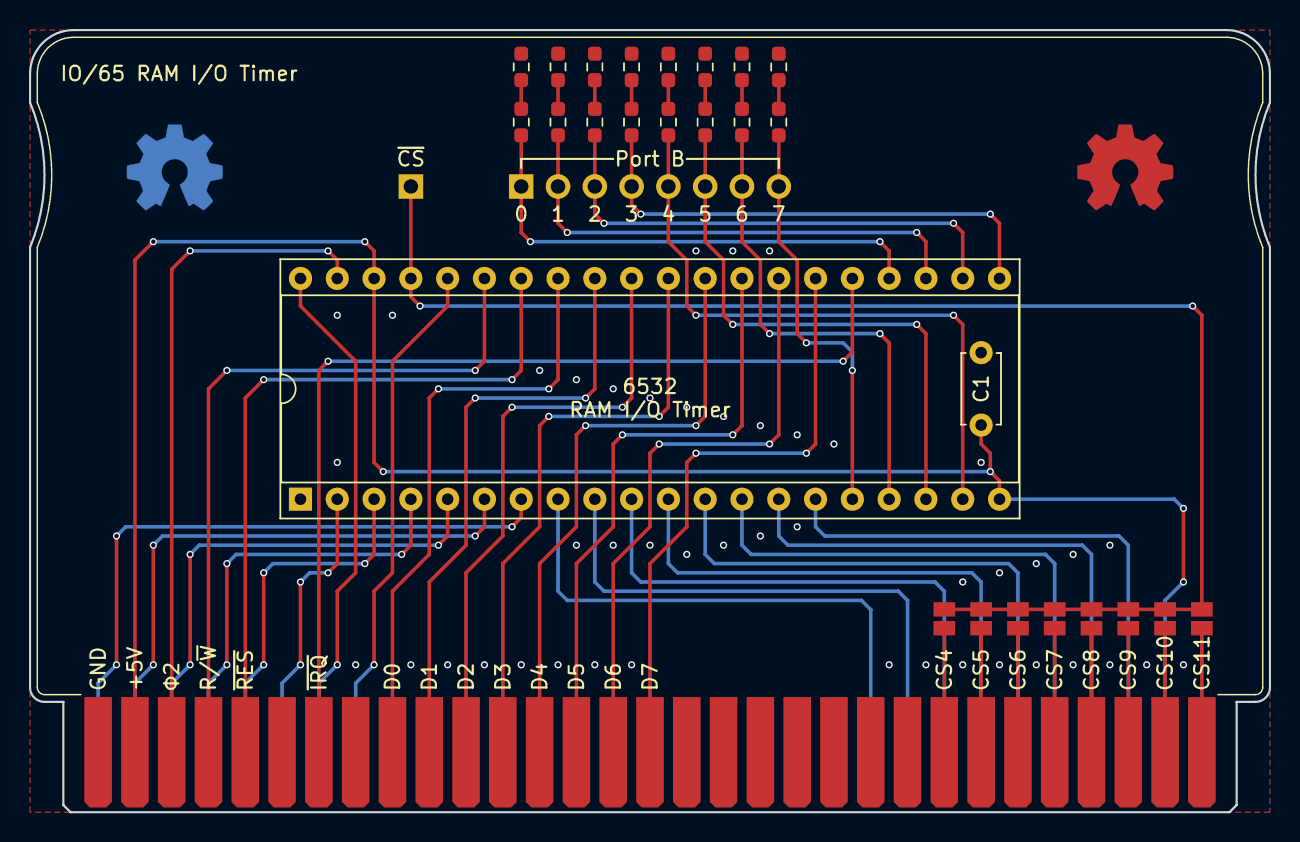
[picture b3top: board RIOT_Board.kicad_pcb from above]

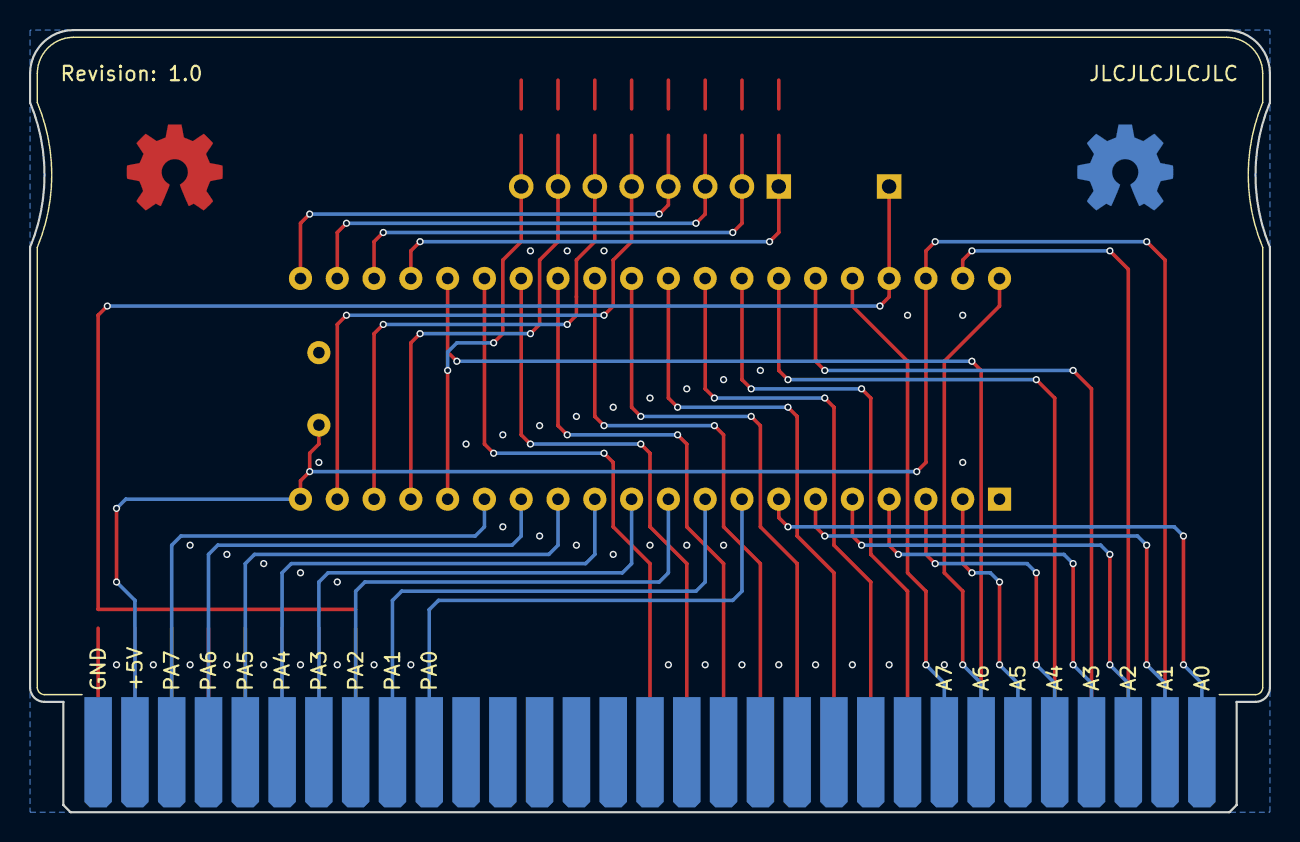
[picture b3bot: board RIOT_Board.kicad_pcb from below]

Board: 2 copper layers, 85.6 x 54.0 mm, 33 parts (4 on the bottom side), 55 nets.

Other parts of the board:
LogoBack: OSHW-Symbol_6.7x6mm_Copper
LogoBackMask: OSHW-Symbol_6.7x6mm_Copper
LogoFront: OSHW-Symbol_6.7x6mm_Copper
LogoFrontMask: OSHW-Symbol_6.7x6mm_Copper
